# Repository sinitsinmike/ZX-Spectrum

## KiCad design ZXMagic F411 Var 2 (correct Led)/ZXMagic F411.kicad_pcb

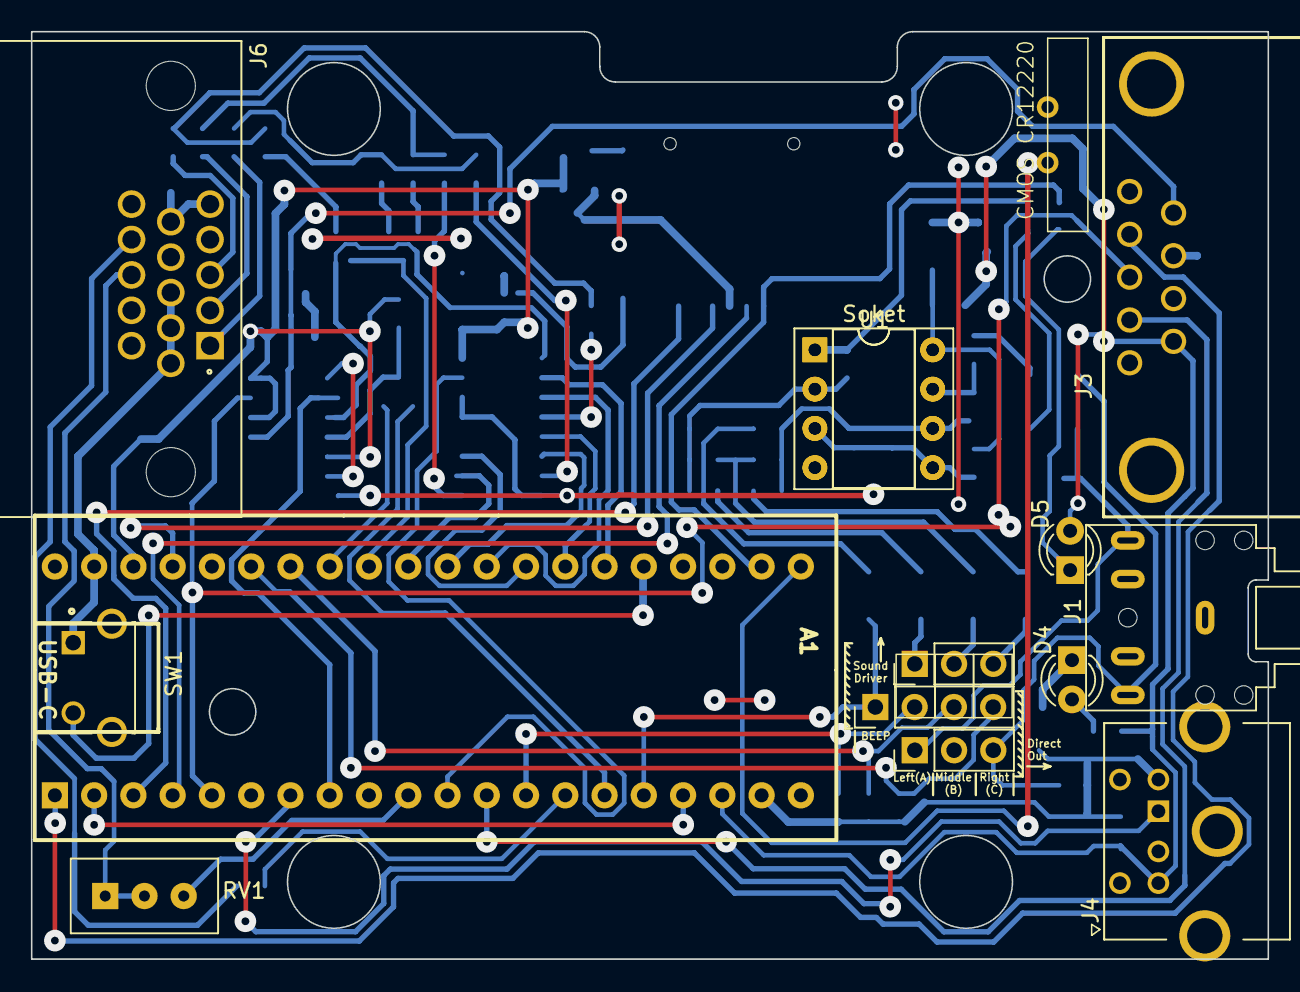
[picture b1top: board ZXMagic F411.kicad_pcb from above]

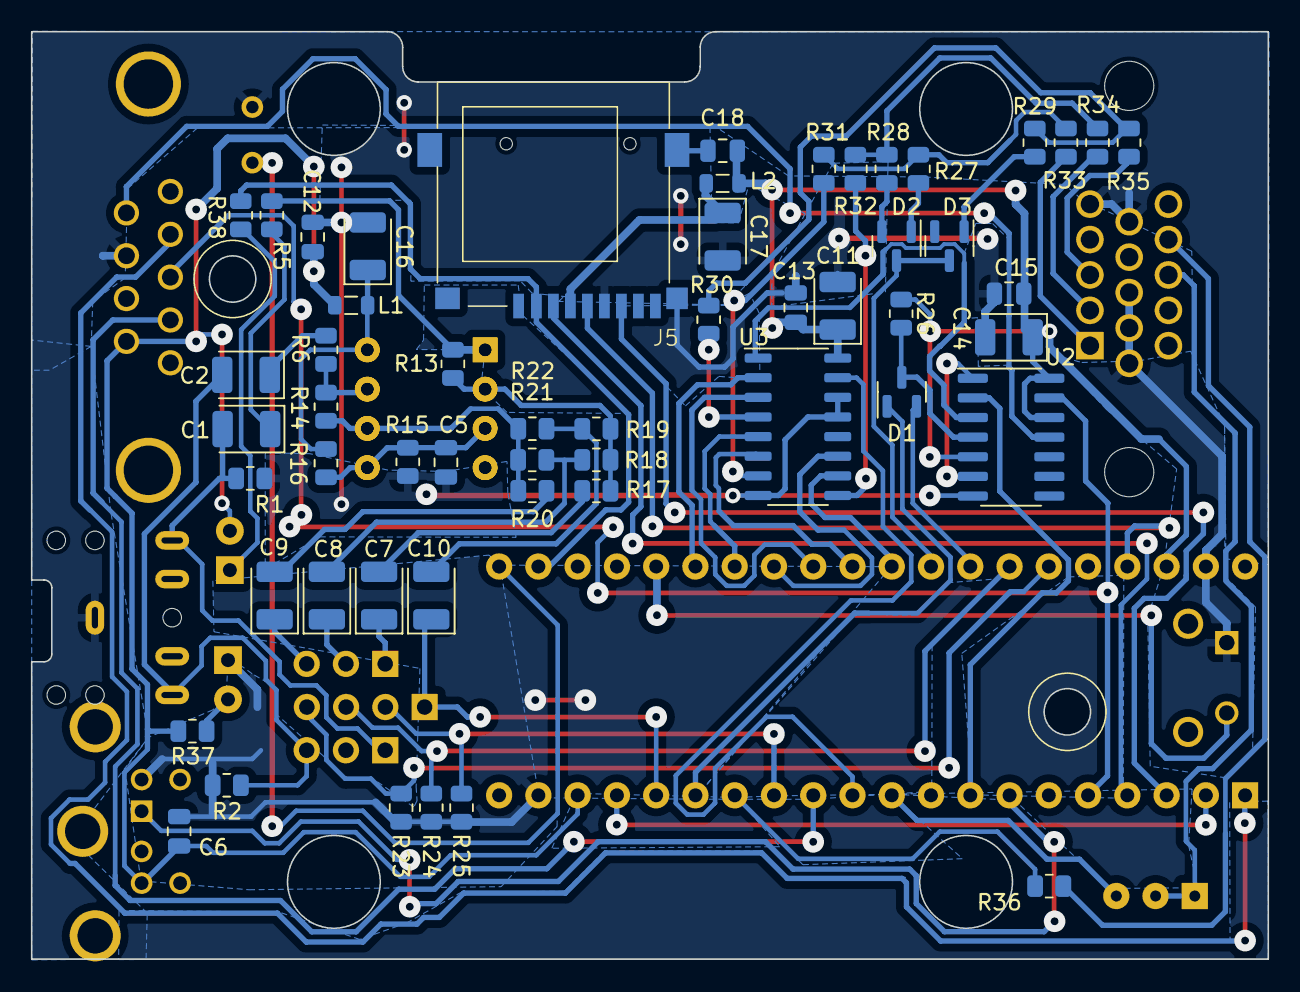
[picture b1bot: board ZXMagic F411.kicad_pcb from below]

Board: 2 copper layers, 80.0 x 60.0 mm, 72 parts (55 on the bottom side), 66 nets.

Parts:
A1: Black_Pill F411CEU6; PCB-STM32F411
C1, C2: 220u; CP_EIA-3528-21_Kemet-B
C5: 10u; C_0805_2012Metric
C6, C12, C13, C15, C18: 0.1u; C_0805_2012Metric
C7, C8, C9: 22u; CP_EIA-3528-21_Kemet-B
C10, C11, C14: 10u; CP_EIA-3528-21_Kemet-B
C16, C17: 47u; CP_EIA-3528-21_Kemet-B
CMOS CR12220: Coin 12.5mm 3 V Lithium Battery
D1: BAT54A; SOT-23
D2, D3: BAT54C; SOT-23
D4, D5: LED; LED_D3.0mm
J1: AudioJack3; Jack_3.5mm_CUI_SJ1-3525N_Horizontal
J3: GamePad (NES); Правильный джой
J4: Mini-DIN-6; PS-2 (Mini Circular DIN 6 pin Connector)
J5: Micro_SD_Card; SD Card Holder 112J-TDAR
J6: VGA; D-SUB 15FR (Видео правильный)
JP_Left: Джампер
JP_MID: Джампер
JP_Right: Джампер
L1, L2: 33u; L_0805_2012Metric
R1, R2: 47k; R_0805_2012Metric
R5, R6: 33; R_0805_2012Metric
R13, R14, R15, R16, R17, R20, R26: 10k; R_0805_2012Metric
R18, R21: 27k; R_0805_2012Metric
R19, R22: 43k; R_0805_2012Metric
R23, R24, R25: 2k; R_0805_2012Metric
R27, R28, R29: 51; R_0805_2012Metric
R30, R31, R32, R38: 180; R_0805_2012Metric
R33, R34, R35: 91; R_0805_2012Metric
R36, R37: 270; R_0805_2012Metric
RV1: 1k; TRIM_3296W-1-102LF
SD Card: SD Card
SW1: Switch SW_TL1105JAF160Q
Soket: DIP-8_W7.62mm_Socket
U1: OPA2134; DIP-8_W7.62mm
U2: 74HC86; SO-14_3.9x8.65mm_P1.27mm
U3: 74HC157; SO-16_3.9x9.9mm_P1.27mm
Верх: Верхний корпус
Низ: Нижний корпус

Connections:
/3v3: A1.20 (+3v3), A1.38 (+3v3), C11.1, C13.1, C14.1, C15.1, C18.1, L2.1, R26.1, U2.5, U2.12, U2.14 (VCC), U3.16 (VCC)
/5V: A1.18 (+5V), A1.40 (+5V), C6.1, C12.1, D5.2 (A), J3.6, J4.4, L1.1, R37.2
/BEEPER: A1.16 (B8), C10.1
/BLANK: A1.11 (B3), U3.15 (OE)
/CHA(Left): A1.13 (B5), C7.1, R25.1
/CHB(Middle): A1.34 (B0), C8.1, R24.1
/CHC(Right): A1.35 (B1), C9.1, R23.1
/CLK_PAD: A1.1 (B12), J3.4
/Data_PAD: A1.12 (B4), J3.2
/FLASH: A1.33 (A7), D1.2
/H_SYNC: A1.10 (A15), RV1.3
/INV: A1.15 (B7), D1.1
/Latch_PAD: A1.5 (A8), J3.3, U2.13
/Latch_PAD2: J3.9, U2.11
/RESET: A1.25 (RST), SW1.2 (B)
/SD3v3: C17.1, J5.4 (VDD), L2.2
/SD_CLK: A1.37 (B10), J5.5 (CLK)
/SD_CS: A1.22 (C13), J5.2 (CS), R38.2
/SOUND5V: C16.1, L1.2, R16.1, U1.8 (V+)
/VBAT: A1.21 (VBAT), CMOS CR12220.1
/V_SYNC: A1.14 (B6), R36.2
GNDD: A1.19 (GND), A1.39 (GND), C5.2, C6.2, C11.2, C12.2, C13.2, C14.2, C15.2, C16.2, C17.2, C18.2, CMOS CR12220.2, D4.1 (K), J1.S, J3.8, J4.3, J5.6 (VSS), J6.5, J6.6, J6.7, J6.8, J6.10, R1.1, R2.1, R15.2, R23.2, R24.2, R25.2, SW1.1 (A), U1.4 (V-), U2.7 (GND), U3.8 (GND), U3.13 (I1c), U3.14 (I0c)
unnamed: A1.26 (A0), U3.2 (I0a)
unnamed: A1.27 (A1), U3.5 (I0b)
unnamed: A1.28 (A2), U3.11 (I0d)
unnamed: A1.29 (A3), U3.3 (I1a)
unnamed: A1.30 (A4), U3.6 (I1b)
unnamed: A1.31 (A5), U3.10 (I1d)
unnamed: A1.32 (A6), D2.3, D3.3
unnamed: A1.7 (A10), J4.1
unnamed: A1.8 (A11), U2.2
unnamed: A1.2 (B13), A1.17 (B9)
unnamed: A1.3 (B14), J5.7 (MISO)
unnamed: A1.4 (B15), J5.3 (MOSI)
unnamed: C1.1, R5.2
unnamed: C1.2, J1.T, R1.2
unnamed: C2.1, R6.2
unnamed: C2.2, J1.R, R2.2
unnamed: C7.2, R17.1
unnamed: C8.2, R18.1, R21.1
unnamed: C9.2, R20.1
unnamed: C10.2, R19.1, R22.1
unnamed: D1.3, R26.2, U2.4
unnamed: D2.1, R27.1
unnamed: D2.2, R28.1
unnamed: D3.1, R29.1
unnamed: D4.2 (A), R37.1
unnamed: D5.1 (K), R38.1
unnamed: J6.1, R33.2
unnamed: J6.2, R34.2
unnamed: J6.3, R35.2
unnamed: J6.13, RV1.1, RV1.2
unnamed: J6.14, R36.1
unnamed: R5.1, R13.2, U1.1
unnamed: R6.1, R14.2, U1.7
unnamed: R27.2, R31.2, R33.1
unnamed: R28.2, R32.2, R34.1
unnamed: R29.2, R30.2, R35.1
unnamed: C5.1, R15.1, R16.2, U1.3 (+), U1.5 (+)
unnamed: R13.1, R17.2, R18.2, R19.2, U1.2 (-)
unnamed: R14.1, R20.2, R21.2, R22.2, U1.6 (-)
unnamed: U2.1, U2.6
unnamed: U2.3, U3.1 (S)
unnamed: R30.1, U3.4 (Za)
unnamed: R31.1, U3.7 (Zb)
unnamed: R32.1, U3.9 (Zd)
